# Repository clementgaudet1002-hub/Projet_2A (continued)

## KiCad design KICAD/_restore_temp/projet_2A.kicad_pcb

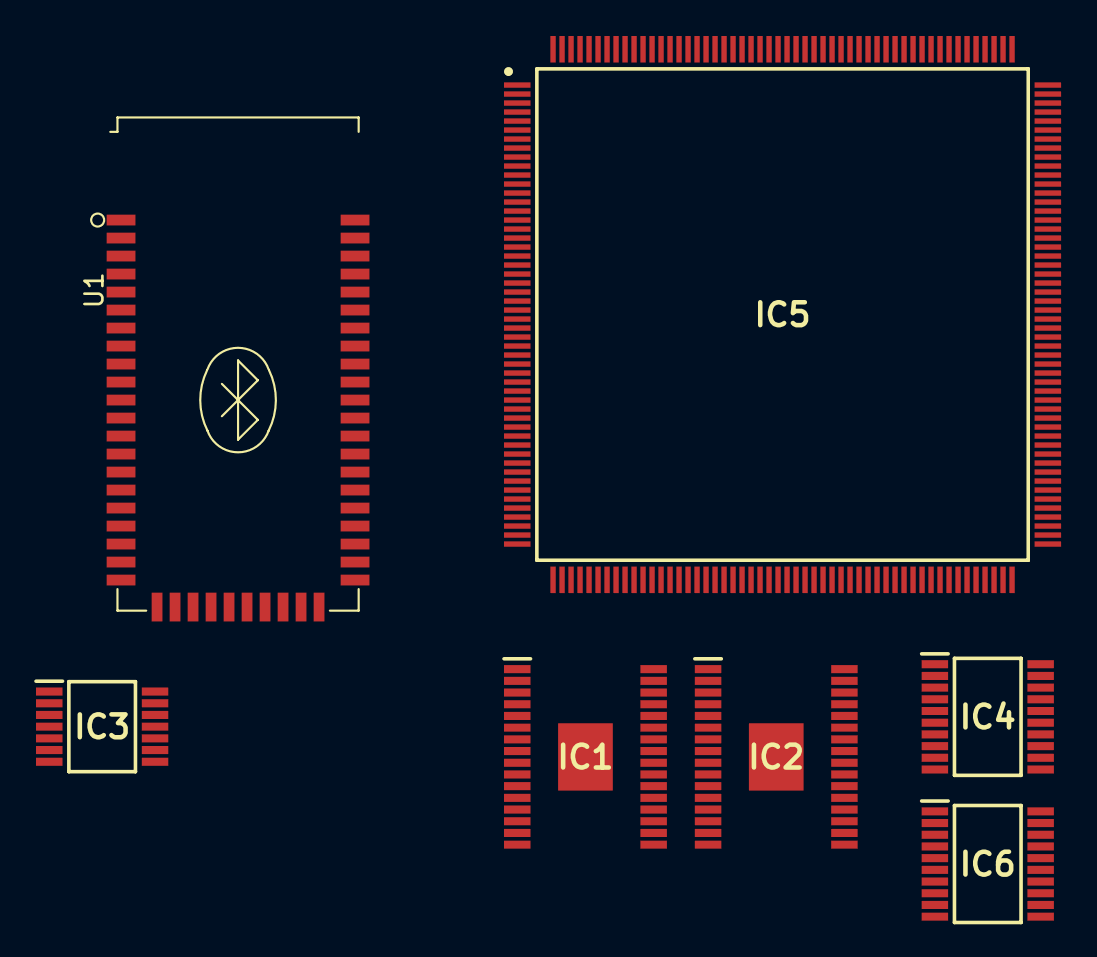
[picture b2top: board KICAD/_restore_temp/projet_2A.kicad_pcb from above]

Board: 2 copper layers, 7 parts (0 on the bottom side), 17 nets, no tracks yet.

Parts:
IC1, IC2: TPA3116D2QDADRQ1
IC3: PCM1808PW
IC4, IC6: PCM5102AQPWRQ1
IC5: STM32F746BGT6
U1: FSC-BT1026E; FSC-BT1026x

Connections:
+3.3V: IC3.4 (VDD), IC4.20 (DVDD), IC6.20 (DVDD), U1.33 (VBAT_IN), U1.34 (SYS_CTRL), U1.36 (VDD_IO)
+3.3VA: IC4.1 (CPVDD), IC4.8 (AVDD), IC6.1 (CPVDD), IC6.8 (AVDD)
/ADC_PCM1808/BCK/SAI1_SCK_A: IC3.8 (BCK), IC4.13 (BCK), IC5.4 (PE5), IC6.13 (BCK)
/ADC_PCM1808/DOUT/SAI1_SD_A: IC3.9 (DOUT), IC5.5 (PE6)
/ADC_PCM1808/LRCK/SAI1_FS_A: IC3.7 (LRCK), IC4.15 (LRCK), IC5.3 (PE4), IC6.15 (LRCK)
/ADC_PCM1808/SCKI/SAI1_MCLK_A: IC3.6 (SCKI), IC5.1 (PE2)
/Bluetooth/USART_RX: IC5.143 (PA9), U1.14 (BT_RX/PI04)
/Bluetooth/USART_TX: IC5.144 (PA10), U1.13 (BT_TX/PI05)
/DAC_PCM5102A/DIN/SAI1_SD_A: IC4.14 (DIN), IC5.2 (PE3), IC6.14 (DIN)
/STM/AMP_MUTE: IC1.12 (MUTE), IC2.12 (MUTE), IC5.54 (PA5)
/STM/AMP_SD: IC1.2 (SD), IC1.3 (FAULT), IC2.2 (SD), IC2.3 (FAULT), IC5.53 (PA4)
GND: IC1.1 (MODSEL), IC1.9 (GND_1), IC1.13 (AM2), IC1.14 (AM1), IC1.15 (AM0), IC1.22 (GND_2), IC1.25 (GND_3), IC1.28 (GND_4), IC1.33 (GND_5), IC2.1 (MODSEL), IC2.9 (GND_1), IC2.10 (LINP), IC2.11 (LINN), IC2.13 (AM2), IC2.14 (AM1), IC2.15 (AM0), IC2.22 (GND_2), IC2.25 (GND_3), IC2.28 (GND_4), IC2.33 (GND_5), IC3.2 (AGND), IC3.5 (DGND), IC3.10 (MD0), IC3.11 (MD1), IC3.12 (FMT), IC4.3 (CPGND), IC4.9 (AGND), IC4.10 (DEMP), IC4.11 (FLT), IC4.12 (SCK), IC4.16 (FMT), IC4.19 (DGND), IC6.3 (CPGND), IC6.9 (AGND), IC6.10 (DEMP), IC6.11 (FLT), IC6.16 (FMT), IC6.19 (DGND), U1.1 (GND), U1.22 (GND), U1.32 (GND), U1.46 (AUDIO_HPR_N), U1.48 (AUDIO_HPL_N), U1.50 (GND), U1.52 (GND)
unnamed: IC1.6 (PLIMIT), IC1.7 (GVDD)
unnamed: IC2.6 (PLIMIT), IC2.7 (GVDD)
unnamed: IC2.21 (OUTNL), IC2.23 (OUTPL)
unnamed: IC2.27 (OUTNR), IC2.29 (OUTPR)
PVCC: IC1.17 (AVCC), IC1.18 (PVCC_1), IC1.19 (PVCC_2), IC1.31 (PVCC_3), IC1.32 (PVCC_4), IC2.17 (AVCC), IC2.18 (PVCC_1), IC2.19 (PVCC_2), IC2.31 (PVCC_3), IC2.32 (PVCC_4)

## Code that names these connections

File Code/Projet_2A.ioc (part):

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Mcu.Name=STM32F446R(C-E)Tx
Mcu.Package=LQFP64
Mcu.UserName=STM32F446RETx
PA0-WKUP.GPIOParameters=GPIO_Label
PA0-WKUP.GPIO_Label=ENC_A
PA0-WKUP.Signal=S_TIM2_CH1_ETR
PA1.GPIOParameters=GPIO_Label
PA1.GPIO_Label=ENC_B
PA1.Signal=S_TIM2_CH2
PA10.GPIOParameters=GPIO_Label
PA10.GPIO_Label=BT_TX
PA10.Mode=Asynchronous
PA10.Signal=USART1_RX
PA13.GPIOParameters=GPIO_Label
PA13.GPIO_Label=SWDIO
PA13.Signal=SYS_JTMS-SWDIO
PA14.GPIOParameters=GPIO_Label
PA14.GPIO_Label=SWCLK
PA14.Signal=SYS_JTCK-SWCLK
PA15.GPIOParameters=GPIO_Label
PA15.GPIO_Label=I2S_WS
PA15.Signal=I2S3_WS
PA2.GPIOParameters=GPIO_Label
PA2.GPIO_Label=ENC_SW
PA2.Signal=GPXTI2
PA3.GPIOParameters=GPIO_Label
PA3.GPIO_Label=BTN_USER
PA3.Signal=GPXTI3
PA4.GPIOParameters=GPIO_Label
PA4.GPIO_Label=AMP_PLIMIT
PA4.Signal=COMP_DAC1_group
PA5.GPIOParameters=GPIO_Label
PA5.GPIO_Label=AMP_SUB_PLIMIT
PA5.Signal=COMP_DAC2_group
PA7.GPIOParameters=GPIO_Label
PA7.GPIO_Label=I2S_DIN2
PA7.Signal=I2S1_SD
PA8.GPIOParameters=GPIO_Label
PA8.GPIO_Label=USB_SCL
PA8.Mode=I2C
PA8.Signal=I2C3_SCL
PA9.GPIOParameters=GPIO_Label
PA9.GPIO_Label=BT_RX
PA9.Mode=Asynchronous
PA9.Signal=USART1_TX
PB0.GPIOParameters=GPIO_Label
PB0.GPIO_Label=AMP_SD
PB0.Signal=GPIO_Output
PB1.GPIOParameters=GPIO_Label
PB1.GPIO_Label=AMP_MUTE
PB1.Signal=GPIO_Output
PB10.GPIOParameters=GPIO_Label
PB10.GPIO_Label=AMP_SUB_MUTE
PB10.Signal=GPIO_Output
PB12.GPIOParameters=GPIO_Label
PB12.GPIO_Label=I2S_LRCK
PB12.Signal=I2S2_WS
PB13.GPIOParameters=GPIO_Label
PB13.GPIO_Label=I2S_BCK
PB13.Signal=I2S2_CK
PB15.GPIOParameters=GPIO_Label
PB15.GPIO_Label=I2S_DIN1
PB15.Signal=I2S2_SD
PB2.GPIOParameters=GPIO_Label
PB2.GPIO_Label=AMP_SUB_SD
PB2.Signal=GPIO_Output
PB3.GPIOParameters=GPIO_Label
PB3.GPIO_Label=TFT_SCK
PB3.Signal=I2S1_CK
PB4.GPIOParameters=GPIO_Label
PB4.GPIO_Label=TFT_CS
PB4.Signal=GPIO_Output
PB5.GPIOParameters=GPIO_Label
PB5.GPIO_Label=TFT_MOSI
PB5.Signal=SPI1_MOSI
PB6.GPIOParameters=GPIO_Label
PB6.GPIO_Label=TFT_DC
PB6.Signal=GPIO_Output
PB7.GPIOParameters=GPIO_Label
PB7.GPIO_Label=TFT_RST
PB7.Signal=GPIO_Output
PB8.GPIOParameters=GPIO_Label
PB8.GPIO_Label=TFT_BL
PB8.Signal=S_TIM4_CH3
PC0.GPIOParameters=GPIO_Label
PC0.GPIO_Label=JACK_DET
PC0.Signal=GPXTI0
PC1.GPIOParameters=GPIO_Label
PC1.GPIO_Label=AMP_SUB_SD
PC1.Signal=GPIO_Output
PC10.GPIOParameters=GPIO_Label
PC10.GPIO_Label=I2S_CK
PC10.Signal=I2S3_CK
PC12.GPIOParameters=GPIO_Label
PC12.GPIO_Label=I2S_DOUT
PC12.Signal=I2S3_SD
PC2.GPIOParameters=GPIO_Label
PC2.GPIO_Label=AMP_SUB_MUTE
PC2.Signal=GPIO_Output
PC6.GPIOParameters=GPIO_Label
PC6.GPIO_Label=I2S_SCKI
PC6.Signal=I2S2_MCK
PC8.GPIOParameters=GPIO_Label
PC8.GPIO_Label=USB_ALERT
PC8.Signal=GPXTI8
PC9.GPIOParameters=GPIO_Label
PC9.GPIO_Label=USB_SDA
PC9.Mode=I2C
PC9.Signal=I2C3_SDA
board=custom
